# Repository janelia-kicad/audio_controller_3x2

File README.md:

- [Repository Information](#orgaf0de10)
  - [Description](#org4f757df)
- [Images](#org2f2734c)
- [Schematic](#org883ee39)
- [Gerbers](#org9caf1d8)
- [Bill of Materials](#org3ae238b)
  - [PCB Parts](#org8b46f87)
  - [Supplemental Parts](#orgfcb51ff)
  - [Vendor Parts Lists](#org931e373)
- [Supplemental Documentation](#orga858066)
  - [Assembly Instructions](#orgc4d95c2)

# Repository Information

-   **Name:** audio\_controller\_3x2
-   **Version:** 1.2
-   **License:** Open-Source Hardware
-   **URL:** <https://github.com/janelia-kicad/audio_controller_3x2>
-   **Author:** Peter Polidoro
-   **Email:** peter@polidoro.io

## Description

This board plays audio through a pcb mounted speaker and/or external stereo speakers.

# Images

# Schematic

[./schematic/audio\_controller\_3x2.pdf](./schematic/audio_controller_3x2.pdf)

# Gerbers

Send gerbers zip file to your favorite PCB manufacturer for fabrication.

[./gerbers/audio\_controller\_3x2\_v1.2.zip](./gerbers/audio_controller_3x2_v1.2.zip)

# Bill of Materials

## PCB Parts

| Item | Reference(s) | Quantity | PartNumber            | Vendor  | Description                                                             |
|---- |------------ |-------- |--------------------- |------- |----------------------------------------------------------------------- |
| 1    | C1 C13 C3 C6 | 4        | 399-13229-1-ND        | digikey | CAP CER 0.1UF 100V X7R 1210                                             |
| 2    | C10 C11      | 2        | 399-8219-1-ND         | digikey | CAP CER 1UF 100V X7R 1210                                               |
| 3    | C12 C2 C5 C7 | 4        | 478-3591-1-ND         | digikey | 2.2uF 50V Ceramic Capacitor X7R 1210                                    |
| 4    | C4           | 1        | 399-15599-1-ND        | digikey | 0.15uF 100V Ceramic Capacitor X7R 1210                                  |
| 5    | C8 C9        | 2        | 478-5964-1-ND         | digikey | CAP CER 3300PF 2KV X7R 1210                                             |
| 6    | J1           | 1        | CP-3523SJCT-ND        | digikey | 3.50mm Headphone Phone Jack Stereo Connector Solder                     |
| 7    | L1           | 1        | 587-1755-1-ND         | digikey | FERRITE BEAD 600 OHM 1210 1LN                                           |
| 8    | MDB1         | 2        | S1011E-16-ND          | digikey | 16 Position Header Through Hole Male Pins                               |
| 9    | R1 R2 R3 R4  | 4        | P2.21KAACT-ND         | digikey | RES SMD 2.21K OHM 1% 1/2W 1210                                          |
| 10   | SP1          | 1        | 102-3539-1-ND         | digikey | SPEAKER 8OHM 300MW TOP PORT 87DB                                        |
| 11   | U1           | 1        | SGTL5000XNAA3R2CT-ND  | digikey | Stereo Audio Interface 32-QFN                                           |
| 12   | U2           | 1        | AP7313-15SAG-7DICT-ND | digikey | Linear Voltage Regulator IC Positive Fixed 1 Output 1.5V 150mA SOT-23-3 |
| 13   | U3           | 1        | LM48310SD/NOPBCT-ND   | digikey | IC AMP AUDIO PWR 2.6W MONO 10SON                                        |

## Supplemental Parts

| Item | Quantity | PartNumber      | Vendor | Description               |
|---- |-------- |--------------- |------ |------------------------- |
| 1    | 1        | N82E16836121042 | newegg | Logitech Z130 5W Speakers |

## Vendor Parts Lists

[./bom/digikey\_parts.csv](./bom/digikey_parts.csv)

[./bom/supplemental\_newegg\_parts.csv](./bom/supplemental_newegg_parts.csv)

# Supplemental Documentation

## Assembly Instructions

-   Solder surface mount and through hole components onto the pcb.

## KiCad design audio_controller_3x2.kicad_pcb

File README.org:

# Created 2018-05-18 Fri 09:57
#+OPTIONS: title:nil author:nil email:nil toc:t |:t ^:nil
* Repository Information

- Name :: audio_controller_3x2
- Version :: 1.2
- License :: Open-Source Hardware
- URL :: https://github.com/janelia-kicad/audio_controller_3x2
- Author :: Peter Polidoro
- Email :: peter@polidoro.io

** Description

This board plays audio through a pcb mounted speaker and/or external stereo
speakers.

* Images

[[file:./images/top.png]]

[[file:./images/bottom.png]]

* Schematic

[[file:./schematic/audio_controller_3x2.pdf][./schematic/audio_controller_3x2.pdf]]

[[file:./schematic/images/schematic00.png]]

* Gerbers

Send gerbers zip file to your favorite PCB manufacturer for fabrication.

[[file:./gerbers/audio_controller_3x2_v1.2.zip][./gerbers/audio_controller_3x2_v1.2.zip]]

[[file:./gerbers/images/gerbers00.png]]

[[file:./gerbers/images/gerbers01.png]]

* Bill of Materials

** PCB Parts

| Item | Reference(s) | Quantity | PartNumber            | Vendor  | Description                                                             |
|------+--------------+----------+-----------------------+---------+-------------------------------------------------------------------------|
|    1 | C1 C13 C3 C6 |        4 | 399-13229-1-ND        | digikey | CAP CER 0.1UF 100V X7R 1210                                             |
|    2 | C10 C11      |        2 | 399-8219-1-ND         | digikey | CAP CER 1UF 100V X7R 1210                                               |
|    3 | C12 C2 C5 C7 |        4 | 478-3591-1-ND         | digikey | 2.2uF 50V Ceramic Capacitor X7R 1210                                    |
|    4 | C4           |        1 | 399-15599-1-ND        | digikey | 0.15uF 100V Ceramic Capacitor X7R 1210                                  |
|    5 | C8 C9        |        2 | 478-5964-1-ND         | digikey | CAP CER 3300PF 2KV X7R 1210                                             |
|    6 | J1           |        1 | CP-3523SJCT-ND        | digikey | 3.50mm Headphone Phone Jack Stereo Connector Solder                     |
|    7 | L1           |        1 | 587-1755-1-ND         | digikey | FERRITE BEAD 600 OHM 1210 1LN                                           |
|    8 | MDB1         |        2 | S1011E-16-ND          | digikey | 16 Position Header Through Hole Male Pins                               |
|    9 | R1 R2 R3 R4  |        4 | P2.21KAACT-ND         | digikey | RES SMD 2.21K OHM 1% 1/2W 1210                                          |
|   10 | SP1          |        1 | 102-3539-1-ND         | digikey | SPEAKER 8OHM 300MW TOP PORT 87DB                                        |
|   11 | U1           |        1 | SGTL5000XNAA3R2CT-ND  | digikey | Stereo Audio Interface 32-QFN                                           |
|   12 | U2           |        1 | AP7313-15SAG-7DICT-ND | digikey | Linear Voltage Regulator IC Positive Fixed 1 Output 1.5V 150mA SOT-23-3 |
|   13 | U3           |        1 | LM48310SD/NOPBCT-ND   | digikey | IC AMP AUDIO PWR 2.6W MONO 10SON                                        |

** Supplemental Parts

| Item | Quantity | PartNumber      | Vendor | Description               |
|------+----------+-----------------+--------+---------------------------|
|    1 |        1 | N82E16836121042 | newegg | Logitech Z130 5W Speakers |

** Vendor Parts Lists

[[file:./bom/digikey_parts.csv][./bom/digikey_parts.csv]]

[[file:./bom/supplemental_newegg_parts.csv][./bom/supplemental_newegg_parts.csv]]

* Supplemental Documentation

** Assembly Instructions

- Solder surface mount and through hole components onto the pcb.

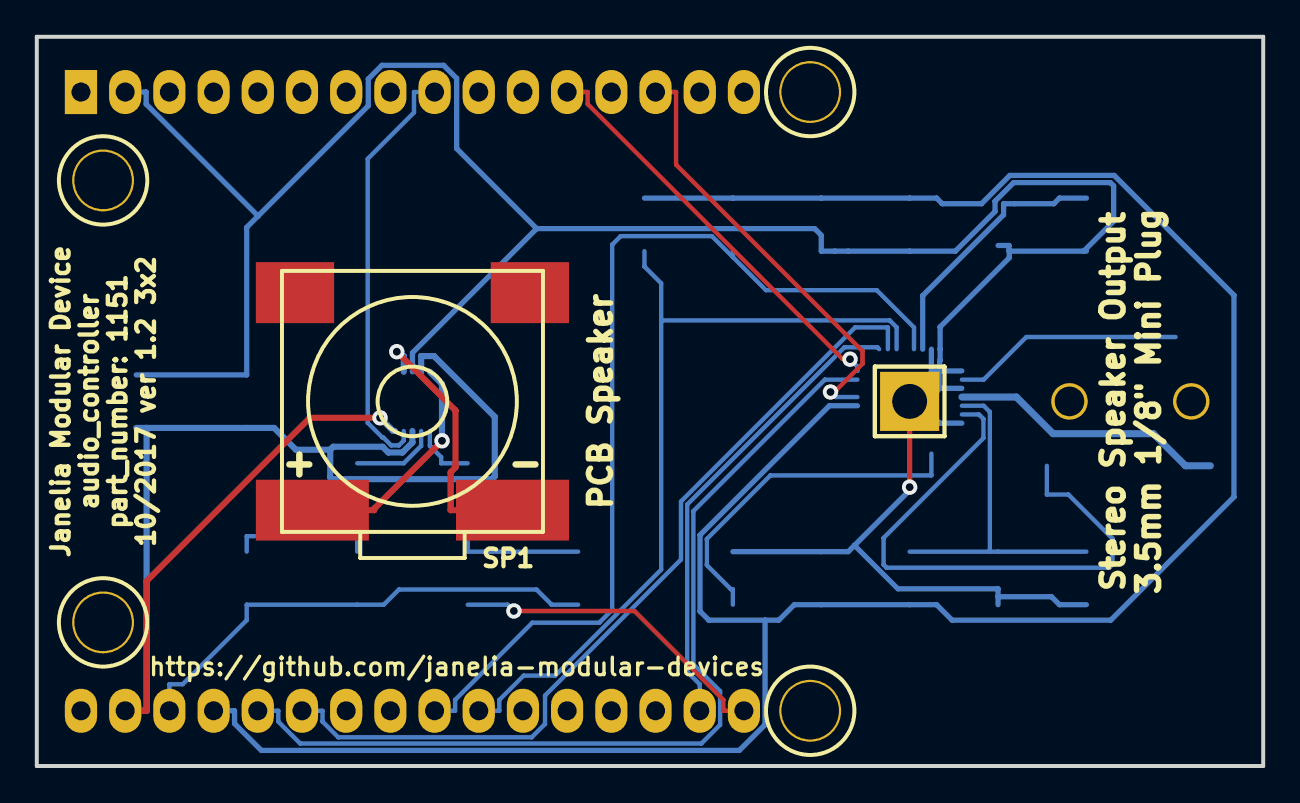
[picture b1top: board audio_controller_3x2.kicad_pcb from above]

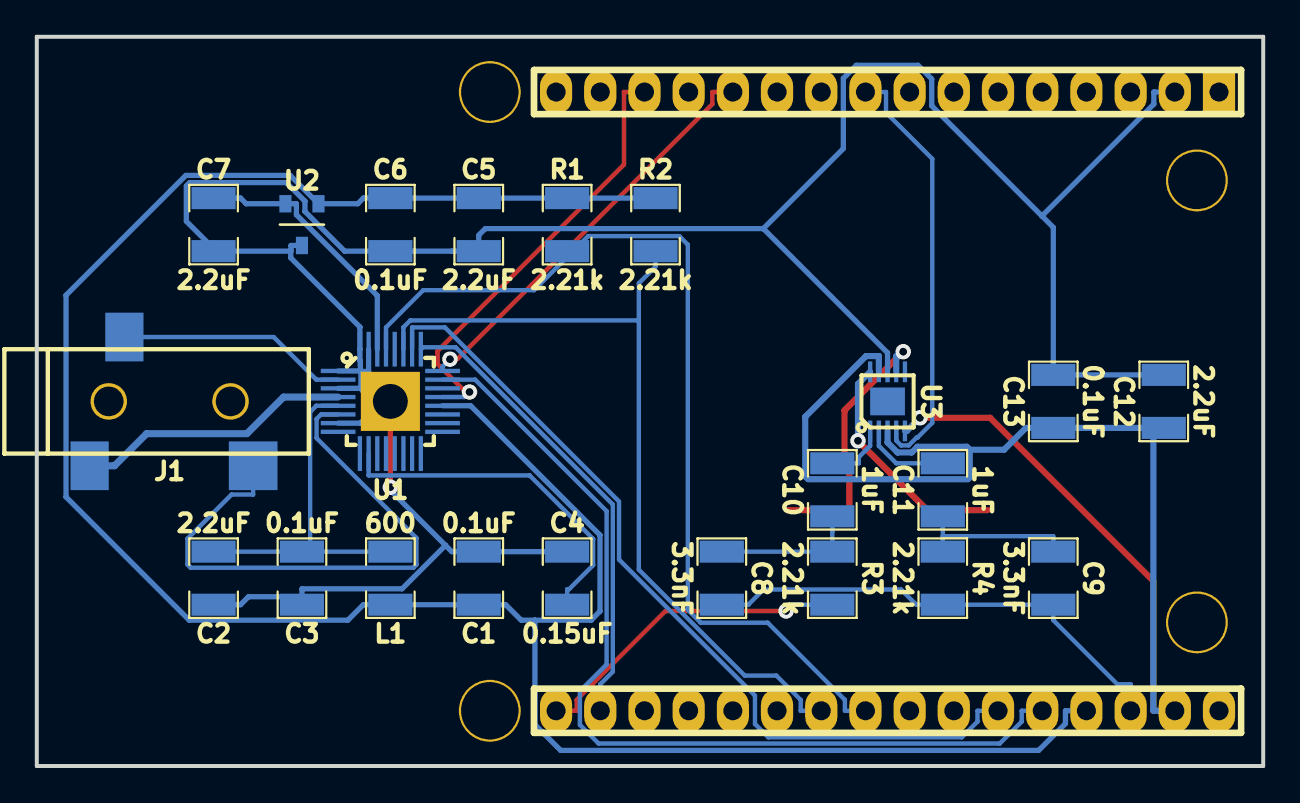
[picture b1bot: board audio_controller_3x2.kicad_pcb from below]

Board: 2 copper layers, 70.5 x 41.9 mm, 24 parts (22 on the bottom side), 25 nets.

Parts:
C1, C3, C6, C13: 0.1uF; SM1210
C2, C5, C7, C12: 2.2uF; SM1210
C4: 0.15uF; SM1210
C8, C9: 3.3nF; SM1210
C10, C11: 1uF; SM1210
J1: AUDIO_JACK_3.5MM; AUDIO_JACK_3.5MM_3PIN
L1: 600; SM1210
MDB1: MODULAR_DEVICE_BASE_3X2_MALE
R1, R2, R3, R4: 2.21k; SM1210
SP1: SPEAKER_8OHM_300MW
U1: SGTL5000; QFN-5x5-32
U2: AP7313_1.5V; SOT-23-3
U3: LM48310; 10-WFDFN_EXPOSED_PAD

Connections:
+1V5: C7.1, U1.30, U2.2
+3V3: C1.1, C5.1, C6.1, L1.1, MDB1.3V3, R1.1, R2.1, U1.20, U2.1
/AGND: C8.2, C9.2, MDB1.AGND, R4.2
/AMP+: SP1.1, U3.10
/AMP-: SP1.2, U3.7
/BCLK: MDB1.9, U1.24
/DAC: MDB1.DAC, R3.2
/HP_L: J1.2, U1.6
/HP_R: J1.3, U1.2
/HP_VGND: J1.1, U1.4
/I2SRX: MDB1.13, U1.25
/I2STX: MDB1.22, U1.26
/LRCLK: MDB1.23, U1.23
/MCLK: MDB1.11, U1.21
/PCB_SPEAKER_ENABLE: MDB1.6, U3.4
/SCL: MDB1.19, R1.2, U1.29
/SDA: MDB1.18, R2.2, U1.27
GND: C1.2, C2.2, C3.2, C4.2, C5.2, C6.2, C7.2, C12.2, C13.2, MDB1.GND, U1.1, U1.3, U1.7, U1.31, U1.32, U1.PAD, U2.3, U3.8
unnamed: C2.1, C3.1, L1.2, U1.5
unnamed: C4.1, U1.10
unnamed: C8.1, C10.1, R3.1
unnamed: C10.2, U3.1
unnamed: C9.1, C11.1, R4.1
unnamed: C11.2, U3.2
VEE: C12.1, C13.1, MDB1.VEE, U3.3, U3.5, U3.9

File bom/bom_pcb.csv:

Item,Reference(s),Value,Quantity,Description,PartNumber,Vendor
1,C1 C13 C3 C6,0.1uF,4,CAP CER 0.1UF 100V X7R 1210,399-13229-1-ND,digikey
2,C10 C11,1uF,2,CAP CER 1UF 100V X7R 1210,399-8219-1-ND,digikey
3,C12 C2 C5 C7,2.2uF,4,2.2uF 50V Ceramic Capacitor X7R 1210,478-3591-1-ND,digikey
4,C4,0.15uF,1,0.15uF 100V Ceramic Capacitor X7R 1210,399-15599-1-ND,digikey
5,C8 C9,3.3nF,2,CAP CER 3300PF 2KV X7R 1210,478-5964-1-ND,digikey
6,J1,AUDIO_JACK_3.5MM,1,3.50mm Headphone Phone Jack Stereo Connector Solder,CP-3523SJCT-ND,digikey
7,L1,600@100MHz,1,FERRITE BEAD 600 OHM 1210 1LN,587-1755-1-ND,digikey
8,MDB1,MODULAR_DEVICE_BASE_3X2_MALE,2,16 Position Header Through Hole Male Pins,S1011E-16-ND,digikey
9,R1 R2 R3 R4,2.21k,4,RES SMD 2.21K OHM 1% 1/2W 1210,P2.21KAACT-ND,digikey
10,SP1,SPEAKER_8OHM_300MW,1,SPEAKER 8OHM 300MW TOP PORT 87DB,102-3539-1-ND,digikey
11,U1,SGTL5000,1,Stereo Audio Interface 32-QFN,SGTL5000XNAA3R2CT-ND,digikey
12,U2,AP7313_1.5V,1,Linear Voltage Regulator IC Positive Fixed 1 Output 1.5V 150mA SOT-23-3,AP7313-15SAG-7DICT-ND,digikey
13,U3,LM48310,1,IC AMP AUDIO PWR 2.6W MONO 10SON,LM48310SD/NOPBCT-ND,digikey

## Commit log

2017-03-24 Initial commit.
2017-03-24 Updated documentation.
2017-03-24 Progress towards v1.0.
2017-03-27 Finished version 1.0.
2017-06-15 Removed .cmp file.
2017-07-14 Moved edge positions.
2017-09-13 Added SPEAKER_8OHM_300MW.kicad_mod.
2017-09-13 Added LM48310.
2017-09-13 Updated 0.1uF capacitors.
2017-09-13 Added speaker and amplifier.
2017-09-14 Finished v1.1.
2017-09-14 Updated gerber zip file.
2017-09-22 Removed extra libraries.
2017-10-05 Fixed 0.15uF part number.
2017-10-17 Progress towards v1.2.
2017-10-19 Finished version 1.2.
2018-01-08 Updated to v4.
2018-01-08 Added v4 files.
2018-01-08 Removed *cache* and *rescue*.
2018-01-08 Updated gitignore.
2018-04-12 README.md -> README.org.
2018-04-19 Added .DS_Store to .gitignore.
2018-05-16 Added images.
2018-05-16 Added generate_kicad_documentation.
2018-05-17 Updated submodules.
2018-08-12 Marked extra Teensy pins.
2018-08-12 Removed v4 files.
2018-08-24 Removed F.SilkS from pads.
2018-11-02 Added README.md.
2021-09-16 Update email address
2021-09-21 Remove ignored files
2022-02-22 Add guix files
2022-02-23 Add guix documentation
